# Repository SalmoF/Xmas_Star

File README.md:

# Xmas_Star
A star shaped PCB with an integrated ATMEGA32U4, an high precision temperature sensor, ToF sensor and LEDs.
Realized for the Christmas PCB challenge by JLCPCB (https://jlcpcb.com)

The device has two operation modes selectable by the on board DIP switch, the default mode the PCB act as a normal
Christmas ornament with its 5 yellow LEDs and an RGB making various light effects (user button used to switch effects manually).
With the second operation mode the device work as a smart device for keeping the distance of a meter and an half 
using a ToF sensor (VL53L1) for every distance above 2 meters the RGB blinks green every 20sec, above 1.5meter green
and yellow toggle each 15 sec, above 1 meter yellow every 10sec and below a meter red blinking every second.
Then if you press the user button the device will start reading the temperature.

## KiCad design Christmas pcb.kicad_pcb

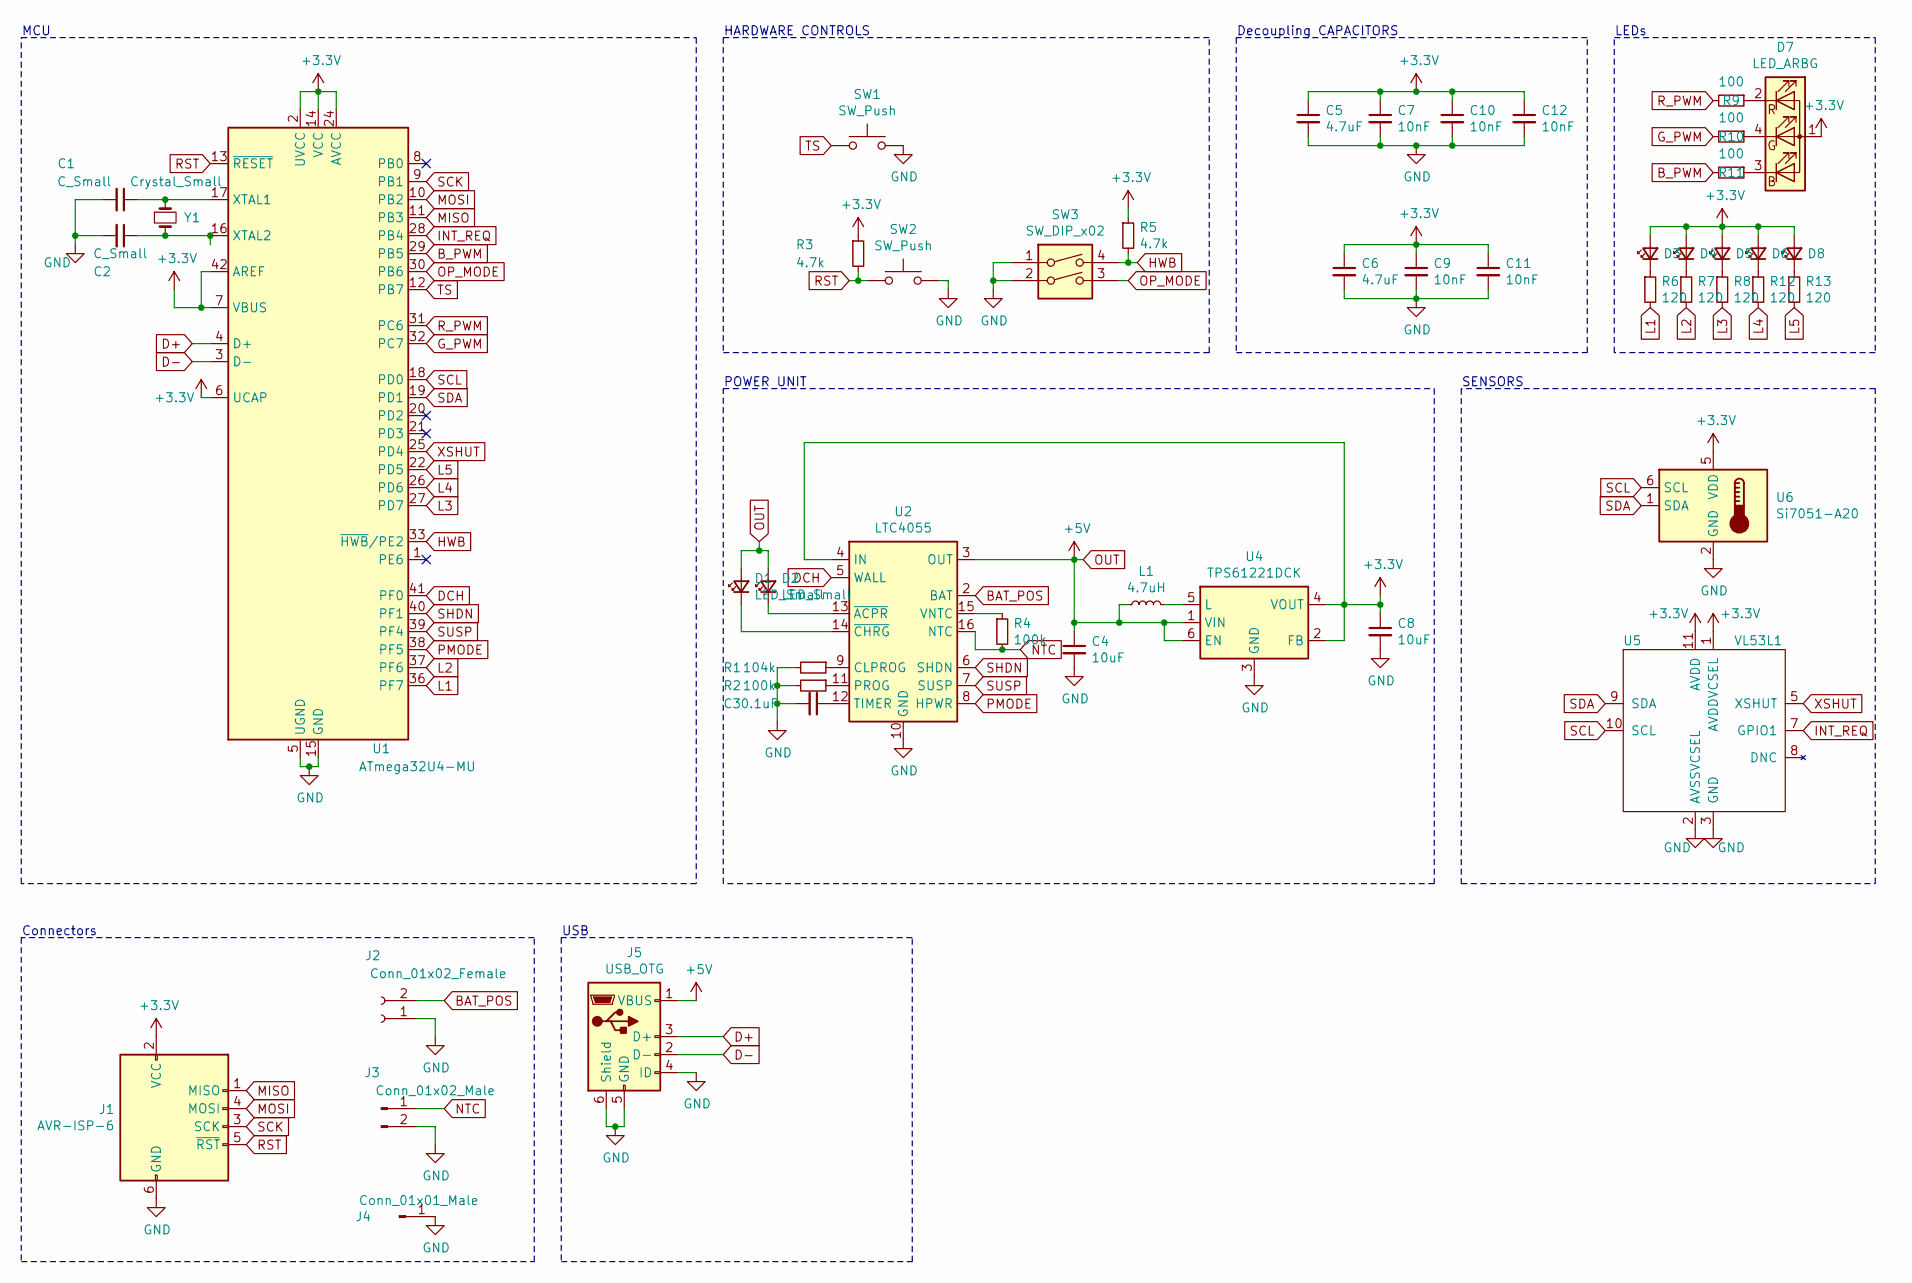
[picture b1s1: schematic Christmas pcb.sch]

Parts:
C1, C2: C_Small; C_0603_1608Metric
C3: 0.1uF; C_0603_1608Metric
C4: 10uF; C_0805_2012Metric
C5, C6: 4.7uF; C_0805_2012Metric
C7, C9, C10, C11, C12: 10nF; C_0603_1608Metric
C8: 10uF; C_0603_1608Metric
D1, D2, D3, D4, D5, D6, D8: LED_Small; LED_0603_1608Metric_Castellated
D7: LED_ARBG; LED_WS2812B_PLCC4_5.0x5.0mm_P3.2mm
J1: AVR-ISP-6; PinSocket_2x03_P2.54mm_Vertical_SMD
J2: Conn_01x02_Female; JST_JWPF_B02B-JWPF-SK-R_1x02_P2.00mm_Vertical
J3: Conn_01x02_Male; JST_JWPF_B02B-JWPF-SK-R_1x02_P2.00mm_Vertical
J4: Conn_01x01_Male; Pin_D1.0mm_L10.0mm
J5: USB_OTG; USB_Micro-AB_Molex_47590-0001
L1: 4.7uH; L_Bourns-SRN4018
R1: 104k; R_0603_1608Metric_Pad1.05x0.95mm_HandSolder
R2, R4: 100k; R_0603_1608Metric_Pad1.05x0.95mm_HandSolder
R3, R5: 4.7k; R_0603_1608Metric_Pad1.05x0.95mm_HandSolder
R6, R7, R8, R12, R13: 120; R_0603_1608Metric_Pad1.05x0.95mm_HandSolder
R9, R10, R11: 100; R_0603_1608Metric_Pad1.05x0.95mm_HandSolder
SW1, SW2: SW_Push; SW_SPST_FSMSM
SW3: SW_DIP_x02; SW_DIP_SPSTx02_Slide_6.7x6.64mm_W6.73mm_P2.54mm_LowProfile_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
U1: ATmega32U4-MU; QFN-44-1EP_7x7mm_P0.5mm_EP5.2x5.2mm
U2: LTC4055; QFN-16-1EP_4x4mm_P0.65mm_EP2.15x2.15mm
U4: TPS61221DCK; Texas_R-PDSO-G6
U5: VL53L1; VL53L1CBV0FY&slash_1
U6: Si7051-A20; DFN-6-1EP_3x3mm_P1mm_EP1.5x2.4mm
Y1: Crystal_Small; Crystal_SMD_MicroCrystal_CC7V-T1A-2Pin_3.2x1.5mm_HandSolder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

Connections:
+3V3: C5.1, C6.1, C7.1, C8.1, C9.1, C10.1, C11.1, C12.1, D3.2 (A), D4.2 (A), D5.2 (A), D6.2 (A), D7.1 (A), D8.2 (A), J1.2 (VCC), R3.1, R5.1, U1.2 (UVCC), U1.6 (UCAP), U1.7 (VBUS), U1.14 (VCC), U1.24 (AVCC), U1.34 (VCC), U1.42 (AREF), U1.44 (AVCC), U2.1 (IN), U2.4 (IN), U4.2 (FB), U4.4 (VOUT), U5.1 (AVDDVCSEL), U5.11 (AVDD), U6.5 (VDD)
BAT_POS: J2.2, U2.2 (BAT)
B_PWM: R11.2, U1.29 (PB5)
D+: J5.3 (D+), U1.4 (D+)
D-: J5.2 (D-), U1.3 (D-)
DCH: U1.41 (PF0), U2.5 (WALL)
GND: C1.2, C2.2, C3.2, C4.2, C5.2, C6.2, C7.2, C8.2, C9.2, C10.2, C11.2, C12.2, J1.6 (GND), J2.1, J3.2, J4.1, J5.4 (ID), J5.5 (GND), J5.6 (Shield), R1.2, R2.2, SW1.2, SW2.2, SW3.1, SW3.2, U1.5 (UGND), U1.15 (GND), U1.23 (GND), U1.35 (GND), U1.43 (GND), U1.45 (GND), U2.10 (GND), U2.17 (GND), U4.3 (GND), U5.2 (AVSSVCSEL), U5.3 (GND), U5.4 (GND2), U5.6 (GND3), U5.12 (GND4), U6.2 (GND)
G_PWM: R10.2, U1.32 (PC7)
HWB: R5.2, SW3.4, U1.33 (~HWB~/PE2)
INT_REQ: U1.28 (PB4), U5.7 (GPIO1)
L1: R6.2, U1.36 (PF7)
L2: R7.2, U1.37 (PF6)
L3: R8.2, U1.27 (PD7)
L4: R12.2, U1.26 (PD6)
L5: R13.2, U1.22 (PD5)
MISO: J1.1 (MISO), U1.11 (PB3)
MOSI: J1.4 (MOSI), U1.10 (PB2)
NTC: J3.1, R4.2, U2.16 (NTC)
unnamed: C1.1, U1.17 (XTAL1), Y1.1
unnamed: C2.1, U1.16 (XTAL2), Y1.2
unnamed: C3.1, U2.12 (TIMER)
unnamed: D1.1 (K), U2.14 (~CHRG)
unnamed: D2.1 (K), U2.13 (~ACPR)
unnamed: D3.1 (K), R6.1
unnamed: D4.1 (K), R7.1
unnamed: D5.1 (K), R8.1
unnamed: D6.1 (K), R12.1
unnamed: D7.2 (RK), R9.1
unnamed: D7.3 (BK), R11.1
unnamed: D7.4 (GK), R10.1
unnamed: D8.1 (K), R13.1
unnamed: L1.2, U4.5 (L)
unnamed: R1.1, U2.9 (CLPROG)
unnamed: R2.1, U2.11 (PROG)
unnamed: R4.1, U2.15 (VNTC)
OP_MODE: SW3.3, U1.30 (PB6)
OUT: C4.1, D1.2 (A), D2.2 (A), J5.1 (VBUS), L1.1, U2.3 (OUT), U4.1 (VIN), U4.6 (EN)
PMODE: U1.38 (PF5), U2.8 (HPWR)
RST: J1.5 (~RST), R3.2, SW2.1, U1.13 (~RESET)
R_PWM: R9.2, U1.31 (PC6)
SCK: J1.3 (SCK), U1.9 (PB1)
SCL: U1.18 (PD0), U5.10 (SCL), U6.6 (SCL)
SDA: U1.19 (PD1), U5.9 (SDA), U6.1 (SDA)
SHDN: U1.40 (PF1), U2.6 (SHDN)
SUSP: U1.39 (PF4), U2.7 (SUSP)
TS: SW1.1, U1.12 (PB7)
XSHUT: U1.25 (PD4), U5.5 (XSHUT)

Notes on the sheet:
USB
POWER UNIT
Connectors
MCU
HARDWARE CONTROLS
SENSORS
LEDs
Decoupling CAPACITORS

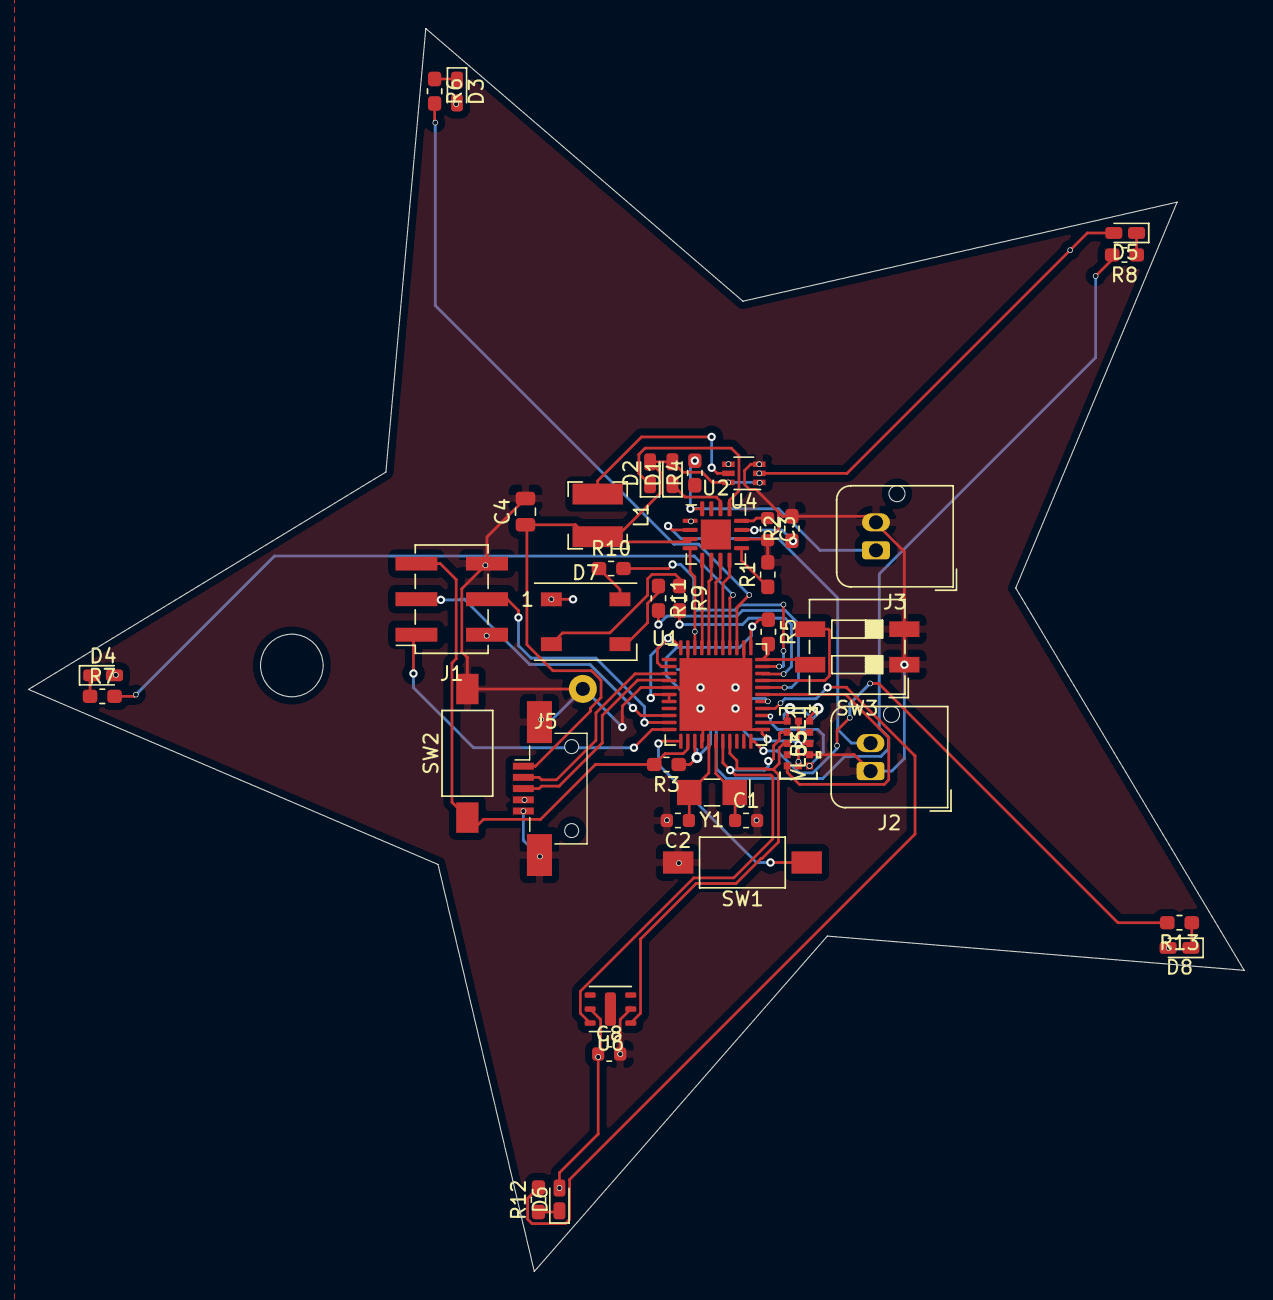
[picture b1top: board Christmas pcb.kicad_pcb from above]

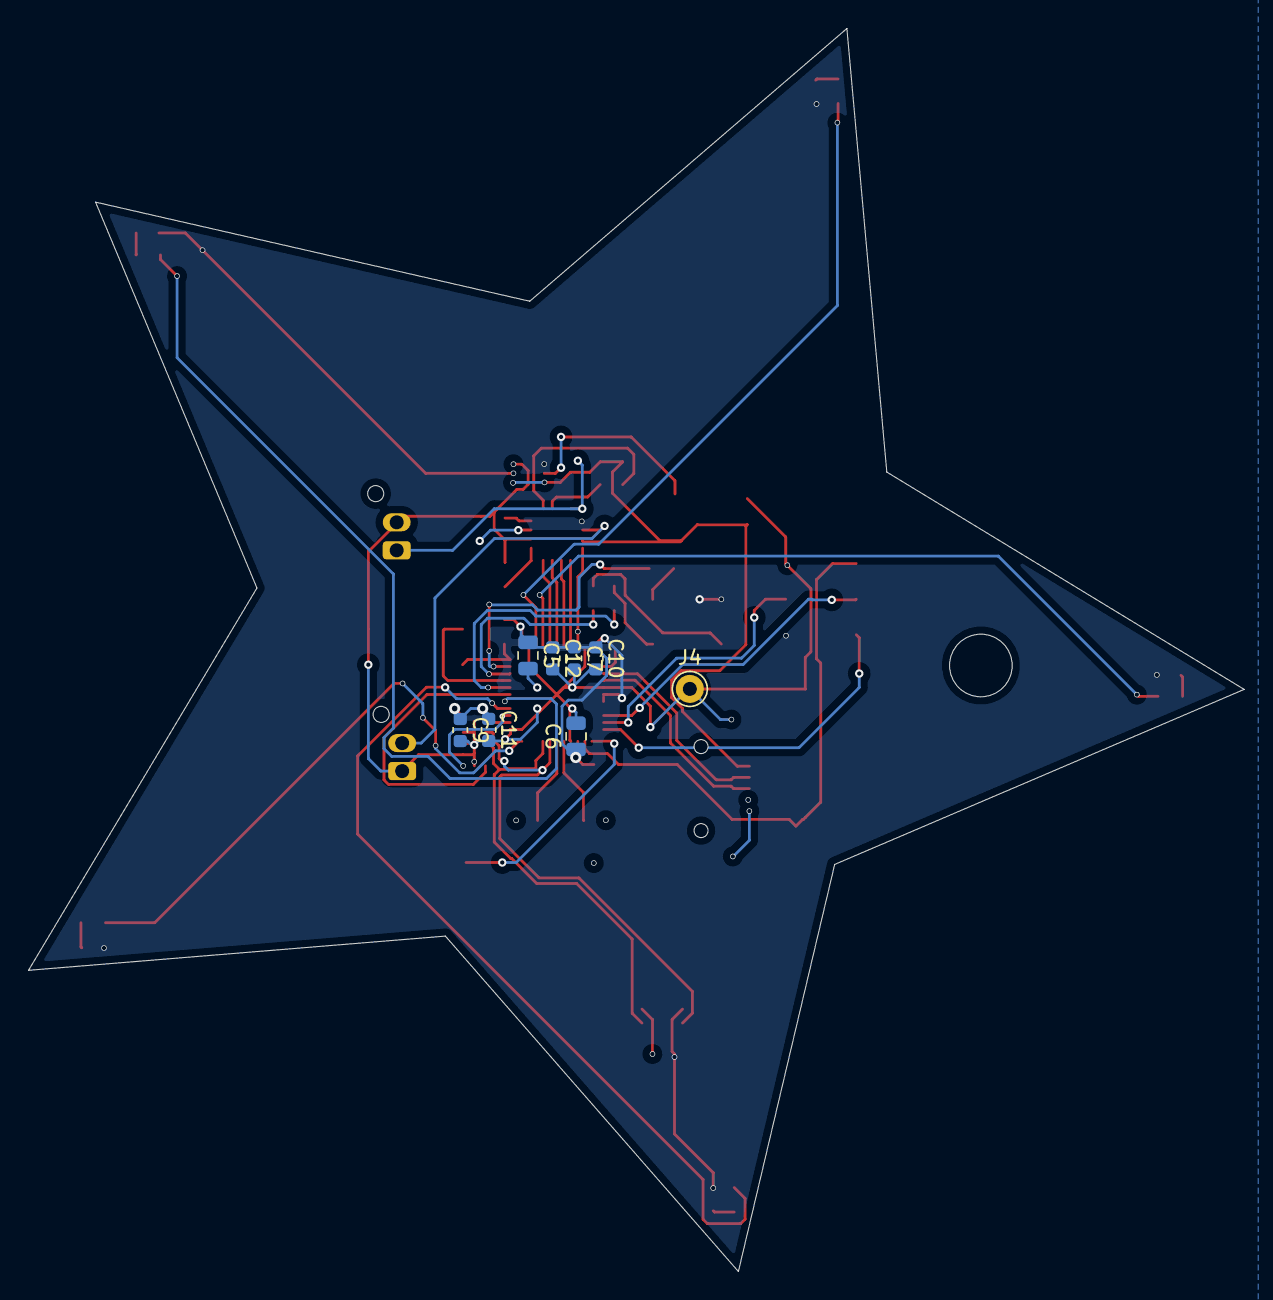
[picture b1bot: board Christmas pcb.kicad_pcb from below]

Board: 2 copper layers, 86.8 x 88.8 mm, 48 parts (8 on the bottom side), 47 nets.

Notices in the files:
parts and their libraries:
Copyright 2016 Accelerated Designs. All rights reserved.
